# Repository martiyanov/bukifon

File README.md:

# Букифон (Bukifon) — открытая платформа: сэмплер + синтезатор + модули

**Версия: 0.57.0** · сайт: **https://bukifon.ru/** (канон, HTTPS), `bukifon.com` → 301, зеркало: https://martiyanov.github.io/bukifon/ (см. [`VERSION`](VERSION), [`CHANGELOG.md`](CHANGELOG.md))

**Букифон** — настольный музыкальный инструмент-платформа, который собирается из
доступных компонентов, печатается на 3D-принтере, расширяется модулями и полностью
открыт: схемы (KiCad), прошивка (C++), механика (STL/генератор), документация.

## Народный синтезатор

Букифон задуман как **народный инструмент**: доступный, повторяемый и открытый. Целевые
ориентиры комплекта (без печати и работы): «народный» на ESP32-S3 — **≤ $200**,
«стандарт» на ESP32-P4 — **≤ $300**, «полный» с аналоговыми картриджами — **≤ $400**.
Подробности и cost-down план — [spec/00-vision.md §13](spec/00-vision.md).

## Что это по сути

Один корпус **380 × 210 × 63 мм**, три режима:

- **Sampler** (в духе Elektron Digitakt) — сэмплы, запись/импорт по USB-C и SD,
  срезы, гранулярность, insert-FX, p-locks, условия триггеров;
- **Synth** (в духе Elektron Syntakt) — 4 части, 8 голосов, 4-оп FM, wavetable,
  ZDF-фильтры, лестница Муга, 3D-мод-матрица 16 слотов;
- **Hybrid** — сэмплы как источники синтеза, общий секвенсор и мод-матрица.

Плюс **режим компьютерной клавиатуры/контроллера**: USB-C композит (HID-клавиатура + MIDI +
UAC2 аудио), DAW-режим (16 энкодеров как CC, transport), **Wi-Fi и Bluetooth** (BLE-MIDI,
BLE HID, передача проектов). То есть Букифон — ещё и необычная механическая клавиатура
с 16 ручками.

**Свои модули может писать каждый:** программный модуль (SDK `BukifonModule`, C++/Lua),
аналоговый картридж на шине 26-pin или сменная панельная дека (18 пэдов / 42 клавиши).
Подробнее — [spec/00-vision.md §12](spec/00-vision.md).

## Текущее состояние (v0.57.0)

| Блок | Состояние |
|---|---|
| **Панель v0.4** | 380 × 210 × 3 мм: 42 клавиши Lapka-42 (точная геометрия, ±18°), 16 энкодеров Ø14, экран 5.0″ 800×480 без рамки, 10 mini-jack, 2 фейдера 60 мм; пересечений 0 |
| **Корпус v0.5-B** | **клин 8°**: 380 × 210 × 61.5 мм (перед 32 / зад 61.5), 6 деталей watertight, печать без поддержек 279 г / 18.3 ч, fitcheck 32/0, профиль 1:1 для картонной проверки |
| **EXT в прошивке** | 8 MIDI-треков (CH/PC/vel/len, 1 CC p-lock), clock out/in 24 ppqn, GEN на внешних, live record, save/load EXTP+CRC32, DIN+USB без дублей; UI-вкладка EXT; **407/407 тестов** (`docs/70 §7`) |
| **Микрофон/голос (реализовано)** | PANEL-2 rev.3: **ICS-43434 I2S MEMS** + порт Ø1.8 (122, 5.5) + LED; CORE-2 rev.3: I2S1 GPIO40/41/42 + J19 + 3.5 мм jack/MAX9814/TS5A + SW3 mute; прошивка: захват/запись ≤30 с/битбокс kick-snare-hat/UNDO/приватность/UI MIC; **407/407 тестов** |
| **Идея → звук** | метрики интуитивности в docs/68: time-to-sound ≤10 с, time-to-idea ≤30 с, 0 критических ошибок за 5 мин, blind-тест 5 людей |
| **Module SDK v0.2** | манифест `bukifon.module.v2` (schema/id/version/api/abi/permissions/params/sha256), валидатор + безопасный loader (API/ABI/SHA до исполнения), 2 примера (`mod_tape_delay`, `mod_euclid_arp`), упаковка `--check` |
| **Внешний секвенсор** | **8 MIDI-треков + 4 внутренние партии**: channel/PC/vel/length, clock out/in, p-lock CC, GEN на внешних, live record; паритет с Octatrack по MIDI (`docs/70`) |
| **Философия интерфейса** | «конституция»: 10 принципов, зеркальная карта ручка↔ячейка, грамматика жестов (`docs/68`) |
| **Читаемость** | экран 5″ 800×480 = 188 PPI, пиксель 0.135 мм; шкала 12/18/24–28 px, проверка по угловым минутам и контрасту (`docs/69`) |
| **Демо = панель** | раскладка как у реального синтезатора (16 энкодеров вокруг экрана, 10 джеков сверху, кластеры ±18°, фейдеры между кластерами); проверка `tools/check_demo_layout.js` → LAYOUT OK (`docs/67`) |
| **Внешнее ревью** | ChatGPT-ревью (`tools/chatgpt_review.sh`, Codex) — 10 рисков, 5 изменений; внедрены контекст-строка/HOME/UNDO/COMPARE/Shift-overlay (`docs/reviews/`, `docs/65 §4a`) |
| **UX-паттерны** | исследование синтезаторных практик (Elektron, Kaleidoscope Минкина, Nord/Deluge/OP-1/Push/M8) и рубрика 9/10 — `docs/65`; GEN-страница, мультивыбор, пресеты, A/B, mod-индикация в демо |
| **Home offload** | `tools/home_offload.sh` — rsync+SSH на домашний ПК (8 ядер, RTX 3060); host-тесты прошли там 226/226 |
| **Темы в прошивке** | 4 темы × 12 токенов (docs/62), рендер на токенах, CLI `--theme`, **226/226 тестов** |
| **UI/UX** | 3 итерации, 16 энкодеров (8 страниц + 8 макросов), фейдеры TRACK/SCENE/DJ + Fn, REC-ресемплинг, 4 темы экрана 800×480 (`docs/61–64`) |
| **Кириллица** | 66 глифов 6×8 (А–Я, а–я, Ё/ё), UTF-8 lookup, транслитерация удалена; метрика: max 90 px при ячейке 94 px; 10 скриншотов RU/EN |
| **Локализация** | UI RU/EN: 90+ ключей (`tr()`), переключение и сохранение языка (project v2), **кириллический glyph-пакет 6×8 (66 глифов, транслитерация удалена)**, 10 RU/EN-скриншотов |
| **Хранение** | storage backend (MockFlash/SD/NVS-stub), **атомарная A/B запись** с CRC32 и recovery; project v2, preset bank, язык — через backend; power-cut/bit-flip тесты |
| **Проект v2** | `.bkfp`: 4 партии + 8 EXT-треков + GEN + mic + модули + тема/транспорт, CRC32, миграция v1, транзакционная загрузка |
| **P4 bring-up app** | UART-баннер/чип/PSRAM, I2C-скан 8/8, RGB565-паттерны, engine bench ≤650 µs, I2S MEMS 1 с; **сборка 330 512 Б, 0 warnings** (IDF 5.5, home) |
| **P4 toolchain** | **сборка проверена** на `pole`: ESP-IDF v5.5 → `bukifon_p4.bin` 250 КБ (83 % app-раздела свободно), bootloader+table; PlatformIO P4 по-прежнему не умеет (`docs/59`) |
| **Демо RU/EN** | 256 ключей, переключатель RU/EN (URL `?lang=en`, localStorage), canvas через `t()`; **a11y**: роли/aria, клавиатурные энкодеры/фейдеры/джеки, видимый фокус, live-region; UX-тест 8/8 RU и EN |
| **Веб-демо** | интерактивная модель: [martiyanov.github.io/bukifon/demo](https://martiyanov.github.io/bukifon/demo/) — 42 клавиши, 16 энкодеров, секвенсор, FM-звук, 4 режима (`docs/58`) |
| **Закупки** | единый лист: P1 $426 + PWR $276.92 + LCD-адаптер $72.8 + печать $42 ≈ **$784** с зачётом пересечений (`docs/54`) |
| **Серийники/QR** | `tools/make_labels.py` (A4 3×8, 60×30 мм, QR+manifest), identity 114 B + двухслотовая flash-модель (`docs/55`); **216/216 тестов** |
| **Протокол P1** | 8 сценариев, пороги, пустые таблицы, матрица P4/H743 + CSV-форма (`docs/56`) |
| **LCD-адаптер** | FFC-40 breakout для HotLCD ST7262 (31×0R pinout-jumper, 35 TP, JST подсветки), ERC 0/0 — проверка экрана на стенде до PCB (`docs/49`) |
| **Release bundle** | `tools/make_release_bundle.sh` → 339 файлов / 15 МБ, SHA256SUMS; `RELEASE_BUNDLE.md`, `docs/50` |
| **Медиа** | PNG→JPEG (60 файлов, −83 МБ), SVG→.svg.gz (19, −46 МБ), дубликаты убраны; tracked **71 МБ** (`docs/52`) |
| **Дисплей** | RGB565 поверх RGB888 FPC-40: **TFT-H050A1SVIST4R40** (HotLCD/ST7262, 40-pin, 1000 нит, $18–25), резерв NHD/EJ050NA; DSI — rev.3.1 (`docs/47`) |
| **PWR-стенд** | 13 измерений до PCB (`docs/44`); BOM: база $123.92 + EVM $153 = **$276.92** (вариант A, D-79); breadboard запрещён |
| **Fab dry-run** | 4 пакета `fab/*/rev1-scaffold`: 16 Gerber-слоёв, PTH+NPTH (129/45/45/4 отверстий), CPL⊆BOM, Edge.Cuts, **checker PASS**; `tools/export_fab_dryrun.sh` — проверка пайплайна до заказа |
| **P4 NVS/partitions** | `partitions.csv` (nvs 24K, factory 1 MiB, storage 1 MiB, coredump 64K), real NVS backend, self-test `project.meta`/`lang`; **bin 369 552 Б, 65 % factory свободно** |
| **PCB rev.1: статус** | 0 placeholder, но **328 упрощённых падов** и GND без заливки: полные реальные пассивы/зоны **не проходят DRC** на 200×108 при 373 компонентах — оставлен DRC-clean каркас (0/0); скрипты упаковки/зон сохранены до трассировки после MCU freeze (docs/82 §12, D-105) |
| **PCB rev.1: реальные футпринты** | **0 placeholder**; кастомные `.kicad_mod` (P4-адаптер, C6, MP1584, Choc) + стандартные KiCad (TRS/DC/кнопки/QFN); DRC-классы Default/Power/USB_HS(90 Ω)/Audio/RF; **DRC 0/0**, RULES PASS; план GND-полигонов |
| **PCB rev.1: нетлист + футпринты** | CORE-2 **373 refs/1224 пада** (16 placeholder), PANEL-2 left/right 181/174 (по 21 Choc), PWR-2 128 (0 placeholder); **DRC 0/0**, verify PASS; unconnected — неразведённые цепи |
| **PCB rev.1 scaffolds** | KiCad-каркасы: CORE-2 200×108 6L, PANEL-2 2×180×190 4L, PWR-2 90×70 4L/2oz; Edge.Cuts/NPTH/keepout, **DRC 0/0**, verify ±0.05 мм (`hardware/*/rev1/`) |
| **Раскладка Lapka-42** | клавиши PANEL-2 исправлены: каждая плата — свои 21 (L01–L21 / R01–R21) по spec (остаточное 0.006 мм от Lapka-42), DRC 0/0; превью `docs/assets/panel-lapka-*.png` |
| **Вырезы разъёмов** | **11 задних**: MIDI IN/OUT **TRS-A Ø8.2** (X30/44), DC Ø9 X91, EXP Ø8.2 X120.5, mic Ø8.2 X140, **LINE OUT** (стерео TRS) X160, PHONES X172, AUDIO IN L/R X184/196, **CV5/6** X208/220; SD 12×2, USB-C; перемычки ≥3.8 мм; B-light **228.9 г/11.0 ч**; fitcheck 16/0 |
| **Board-fit (PCB rev.1)** | контуры для KiCad: CORE-2 200×108, PANEL-2 две платы 180×180 (360×190), PWR-2 90×70; DXF/assembly/spec, 22 проверки 0 конфликтов (`mechanical/board-fit/`) |
| **PANEL-2 ∥ панели** | стойки/плата наклонены вместе с панелью: угол **0.00°**, зазор **12 мм**, оси энкодеров/клавиш ⊥ панели; fitcheck B-light **47/0**; B-light **228.9 г/11.0 ч**; `panel_parallel.jpg` |
| **Корпуса** (с микрофоном) | B_mic ≈278 г/18.4 ч, C_mic ≈316 г/20.9 ч (порт/LED/MEMS на панелях; fitcheck 44/0 и 49/0) |
| **Корпуса** | A flat 301 г/19.9 ч · B 8° 275.5 г/18.2 ч · **B-light 228.9 г / 11.0 ч** · C 12° 313.2 г/20.7 ч; B_mic 276.8, C_mic 314.6; PANEL-2 ∥ панели (0.00°) — `docs/45` |
| **Factory test** | 14 тестов, CLI `factory --json`, loopback-плаг, EOL 2–2.5 мин (`docs/46`); **183/183 тестов** |
| **Product BOM P4 (первый SKU)** | `BOM-p4.csv` + `docs/33/40` (rev.3 с микрофоном): COGS **$241/$215/$196** на 1/10/25 (mic-узел $17.6); **P4 Standard $299** (gross 28.1 % на 10, net ~18 %), Full Bundle $399; S3 lite — $224/$199/$181 |
| **Сборка** | `renders/templates/bukifon_assembly_map_1to1.pdf` (4 стр: слои, панель 1:1, крепёж/шлейфы), `docs/34`, `docs/35` print-first, 3D exploded |
| **UI = философия** | 16 ячеек зеркально ручкам, шкала 12/18/24–28 px, контекст-строка, HOME; Cream AA; **263/263 тестов** (`docs/66/68/69`) |
| **GEN/UX в прошивке** | PROB/EUCLID/MUTATE/SCALE/ARP/EVOLVE/SEED (детерминированно), 5-я вкладка GEN, 8 пресетов с CRC32, A/B, мультивыбор, mod-visible «M»; **248/248 тестов** (`docs/66`) |
| **Прошивка v0.7** | **160/160 тестов**; S3 HAL сборка SUCCESS; spike `spike_s3` SUCCESS; **P1 P4-профиль** PASS (RGB/DSI 52 fps, HS UAC2 8×8, max block 320 µs); UI 4 режимов; Module API v0.1 |
| **CORE-2 rev.2 (основная плата)** | ESP32-P4 + ESP32-C6, 32 МБ PSRAM, USB HS, RGB565/DSI, ERC 0/0; DFM/DFT: 30 TP, **21 self-test** (вкл. микрофон), recovery, 6 слоёв — PRE-FREEZE |
| **Корпус B-light** | **228.9 г / 11.0 ч** (−17 % массы, −39 % времени): стенки 2.0/дно 1.8, 3 периметра + локальные рёбра, панели-оболочки; 6 STL watertight, fitcheck **47/0**; PANEL-2 ∥ панели |
| **CORE-2 rev.2** | схема внесена: J17/J18, входы 12V_EXT/N12_EXT/+5V_EXT/5V_LED, EN-развязки, CV IN3/4 на MCP3208, re-pin J14/J15/J16, DNP 46; **ERC 0/0**, pinmap PASS |
| **PANEL-2 rev.2** | J13/J14 (5V_LED, LED_RET, EN_RAILS, EN_LED5), re-pin по канону, GATE_IN на MCP23017 0x23, LED_DATA 3.3 В + shifter; **ERC 0 err/6 warn**, verify 1290/0 |
| **PWR-2 rev.1** | батарея 1S2P + BMS BQ297 + **MAX17048** + рельсы шины: +12 В 330 мА (TPS61088), −12 В 95 мА (LMR33630 IBB), +5 В 1.6 А, +5V_LED; master load-switch, EN рельсов, питание только от BQ24074 OUT/VSYS; ERC **0/0**, PRE-FREEZE |
| **Электроника rev.1** | **CORE-2** (ESP32-P4 + ESP32-C6 Wi-Fi/BLE по SPI, USB HS composite, аудио PCM5102A/PCM1808, CV, MIDI, шина) — ERC **0/0**, pinmap PASS (54/55 GPIO), **PRE-FREEZE**; **PANEL-2** (16 энкодеров + 42 клавиши через 4× MCP23017, LCD, 10 джеков, 2 фейдера, 3 шлейфа) — ERC 0 errors / 6 warnings, **PRE-FREEZE**. Не заказывать до бенчмарка P1 |
| **Прошивка v0.6** | host-демо UI 800×480, секвенсор 4×16 (хранение 8 дорожек), save/load с CRC16, Module API v0, режимы Synth/Sampler/DAW/USB-keyboard, каркасы USB composite и BLE/Wi-Fi; **120/120 тестов**; сборки ESP32-S3 и RP2040; P4 — toolchain пока нет |
| **P1-стенд** | `docs/26` — что купить (P4 EV, H743, S3, PCM5102A/1808, дисплей, SD, БП/нагрузка), схема стенда, протокол измерений и таблица решения; без стенда MCU не фиксируется |
| **Cost-down / первый SKU** | `docs/27`: product BOM вместо «мастерской», S3-base **kit $199** (партия 10–25, direct-sale), P4 $299 после P1, full $399 bundle; батарея — не россыпь 18650 |
| **Бумажный макет** | `renders/templates/bukifon_paperkit_1to1.pdf` (4 стр: панель 1:1 ×2, профиль 8°, карта 7 проверок) + `docs/28` |
| **Бенчмарк P1** | workload freeze + харнесс `firmware/bench` (7 сценариев, JSON/CSV, детерминизм, 0 аллокаций): host worst **218 µs** = 16.4 % дедлайна, 431 µs запаса до критерия 650 µs; `bench_s3` собран; **протокол приёма стендов P4/H743 готов** (`docs/56`, CSV-форма), стенды — следующие |
| **SDK модулей** | Module API v0 (10 функций, лимиты, WCET/bypass), каталог `modules/` (template + gain_fx C++ + LFO Lua), `tools/validate_module.py`, `tools/new_module.sh`, CI `modules.yml` |
| **BOM (draft)** | 92 позиции: база ≈ 21 657 ₽ (~$271), полный ≈ 32 518 ₽ (~$406); «народная» цель ≤ $200 / стандарт ≤ $300 — cost-down план в spec/00 §13 |
| **Безопасность** | история очищена от GPS EXIF и vendor-PDF с IP, санитизация путей, `SECURITY.md`, `tools/security_scan.sh` |

## Ключевые документы

| Документ | О чём |
|---|---|
| [spec/90-requirements-registry.md](spec/90-requirements-registry.md) | реестр требований R-01…, журнал решений D-01… — единственный источник истины |
| [docs/12-roadmap.md](docs/12-roadmap.md) | дорожная карта P0–P8 с числовыми критериями выхода |
| [docs/10-elektron-hardware.md](docs/10-elektron-hardware.md) | что стоит внутри Elektron (ColdFire, DSP56300, SHARC, FPGA) |
| [docs/11-esp32-feasibility.md](docs/11-esp32-feasibility.md) | можно ли на ESP32: расчёт нагрузки, P4/S3/H743/Teensy |
| [docs/03-second-opinion-mcu.md](docs/03-second-opinion-mcu.md) | независимое ревью плана (DeepSeek) |
| [docs/04-consultation-gpt.md](docs/04-consultation-gpt.md) | консультация GPT/Codex (gpt-5.6) по MCU и архитектуре |
| [docs/00-context-transfer.md](docs/00-context-transfer.md) | контекст проекта для передачи другим агентам |
| [PULL_REQUEST.md](PULL_REQUEST.md) | описание MR v0.4 |
| [docs/20-analog-projects.md](docs/20-analog-projects.md) | разведка аналогов (Deluge, M8, Polyend, Daisy, PreenFM, Norns…) |
| [docs/21-ergonomics.md](docs/21-ergonomics.md) | эргономика: клин 8°, 32/61.5 мм, экран 35° |
| [docs/22-night-plan.md](docs/22-night-plan.md) | ночной план и scope freeze |
| [docs/23-nightly-report.md](docs/23-nightly-report.md) | отчёт ночи: что готово/симулируется/нельзя заказывать |
| [docs/24-module-sdk.md](docs/24-module-sdk.md) | SDK модулей: Module API v0, упаковка, ограничения |
| [docs/25-power-architecture.md](docs/25-power-architecture.md) | питание: ±12 В, BQ24074, MAX17048, земля, стенд до PCB |
| [docs/26-p1-bench-kit.md](docs/26-p1-bench-kit.md) | P1-стенд: закупка, схема, протокол измерений, таблица решения MCU |
| [docs/27-costdown.md](docs/27-costdown.md) | cost-down, product BOM, первый SKU S3-kit $199, батарея, дефицит |
| [docs/28-paper-kit.md](docs/28-paper-kit.md) | бумажный макет 1:1 за 30 минут: 7 проверок эргономики |
| [docs/29-p1-order.md](docs/29-p1-order.md) | точный список заказа P1-стенда (что, где, сколько) |
| [docs/54-shopping-list.md](docs/54-shopping-list.md) | **единый закупочный лист**: P1 + PWR + LCD-адаптер + печать, итоги A–D, порядок |
| [docs/30-security-purge.md](docs/30-security-purge.md) | запрос на purge старых PII-объектов GitHub (SHA) |
| [docs/31-core-s3-constraints.md](docs/31-core-s3-constraints.md) | CORE-S3: GPIO 31, 1-bit SD, USB endpoint ceiling, RGB+1FB, TPS63802 |
| [docs/32-progress-report.md](docs/32-progress-report.md) | сводный отчёт v0.4→v0.13.0: вехи, блокеры, следующий шаг |
| [docs/49-lcd-adapter.md](docs/49-lcd-adapter.md) | LCD FFC-40 адаптер и pinout J12 |
| [docs/50-downloads.md](docs/50-downloads.md) | где скачать STL/PDF/BOM/прошивку |
| [docs/51-pwr-log.md](docs/51-pwr-log.md) | журнал 13 измерений PWR и матрица go/no-go |
| [docs/52-media-policy.md](docs/52-media-policy.md) | форматы медиа и размер репозитория |
| [docs/54-shopping-list.md](docs/54-shopping-list.md) | единый закупочный лист до PCB |
| [docs/55-labels-traceability.md](docs/55-labels-traceability.md) | серийники, QR-метки, traceability |
| [docs/56-p1-measurements.md](docs/56-p1-measurements.md) | протокол P1: P4 vs H743 |
| [docs/57-usability-test.md](docs/57-usability-test.md) | тест эргономики на макете |
| [docs/58-web-demo.md](docs/58-web-demo.md) | веб-демо интерфейса и звука |
| [docs/59-p4-toolchain.md](docs/59-p4-toolchain.md) | P4: ESP-IDF scaffold и сборка |
| [docs/60-module-distribution.md](docs/60-module-distribution.md) | упаковка и распространение модулей |
| [docs/61-ui-design.md](docs/61-ui-design.md) | UI/UX: итерации и лучшие практики |
| [docs/62-screen-palette.md](docs/62-screen-palette.md) | палитра экрана 800×480 (4 темы) |
| [docs/63-resampling-looper.md](docs/63-resampling-looper.md) | ресемплинг (v1.0) и луппер (backlog) |
| [docs/64-fader-modes.md](docs/64-fader-modes.md) | режимы фейдеров: Octatrack-сцены, DJ, Fn |
| [docs/65-ux-patterns.md](docs/65-ux-patterns.md) | UX-паттерны синтезаторов, связка с железом, рубрика 9/10 |
| [docs/66-ux-implementation.md](docs/66-ux-implementation.md) | реализация UX-паттернов: GEN, пресеты, A/B, мультивыбор |
| [docs/67-panel-demo-layout.md](docs/67-panel-demo-layout.md) | сверка раскладки демо с панелью v0.4 |
| [docs/68-interface-philosophy.md](docs/68-interface-philosophy.md) | философия интерфейса и продукта (конституция) |
| [docs/69-screen-legibility.md](docs/69-screen-legibility.md) | читаемость экрана 800×480: физика, шрифты, контраст |
| [docs/70-external-sequencer.md](docs/70-external-sequencer.md) | Букифон как секвенсор для внешних синтезаторов |
| [docs/71-mic-voice.md](docs/71-mic-voice.md) | микрофон/голос: запись, битбокс, вокодер, приватность |
| [docs/72-assembly-workshops.md](docs/72-assembly-workshops.md) | где собрать: мастерские Москвы/СПб/НН, RFQ, цены |
| [docs/73-morning-report.md](docs/73-morning-report.md) | утренний отчёт: состояние, блокеры, план, риски |
| [docs/74-usability-test-harness.md](docs/74-usability-test-harness.md) | blind UX-тест: 8 задач, таймер, JSON (`/demo/?test=1`) |
| [docs/75-release-readiness.md](docs/75-release-readiness.md) | ворота G1–G12 до v1.0-rc, статусы, stop/go |
| [docs/76-known-limitations.md](docs/76-known-limitations.md) | честные ограничения v1.0-rc (до покупки) |
| [docs/77-quick-start.md](docs/77-quick-start.md) | быстрый старт: идея за 10 минут |
| [docs/78-support-repair.md](docs/78-support-repair.md) | поддержка/ремонт: диагностика, recovery, запчасти, гарантия |
| [docs/79-competitors-2026.md](docs/79-competitors-2026.md) | аналоги 2025–2026, позиционирование и цены |
| [docs/80-day1-bringup.md](docs/80-day1-bringup.md) | день 1 с железом: PWR→P1→CORE-2, 15 шагов, stop/go |
| [docs/81-faq.md](docs/81-faq.md) · [docs/press/](docs/press/) | FAQ для покупателя · пресс-кит (буилерплейт RU/EN, изображения) |
| [docs/82-pcb-layout-plan.md](docs/82-pcb-layout-plan.md) | план разводки rev.1: стеки, floorplan, DRC/DFM, критичные цепи |
| [docs/83-fab-package.md](docs/83-fab-package.md) · [fab/](fab/) | состав fab-пакета, CPL/BOM, чек-лист, приёмка; `tools/check_fab_package.py` |
| [docs/84-costdown.md](docs/84-costdown.md) | cost-down: где деньги, варианты снижения, маржа $299/$319/$349 |
| [docs/85-second-source.md](docs/85-second-source.md) | вторые источники, supply-риски, чек-лист до заказа |
| [docs/86-backlog-webapp-plugin.md](docs/86-backlog-webapp-plugin.md) | бэклог: сайт на VDS, PWA-приложение, DAW-плагин |
| [docs/91-software-modules.md](docs/91-software-modules.md) | софтовые модули/машины: `.bkm`, USB/SD/Wi-Fi, sandbox, каталог |
| [docs/87-v1.0-rc-notes-draft.md](docs/87-v1.0-rc-notes-draft.md) | черновик release notes v1.0-rc (критерии, проверки) |
| [docs/88-vds-deploy.md](docs/88-vds-deploy.md) | деплой сайта на VDS (bukifon.ru/.com): DNS, TLS, скрипт |
| [docs/en/README.md](docs/en/README.md) · [quick-start](docs/en/quick-start.md) | English docs index / quick start |
| [docs/72-assembly-workshops.md](docs/72-assembly-workshops.md) | где собрать: мастерские Москвы/СПб/НН, RFQ, цены |
| [docs/73-morning-report.md](docs/73-morning-report.md) | утренний отчёт: состояние, блокеры, план, риски |
| [docs/74-usability-test-harness.md](docs/74-usability-test-harness.md) | blind UX-тест: 8 задач, таймер, JSON (`/demo/?test=1`) |
| [docs/75-release-readiness.md](docs/75-release-readiness.md) | ворота G1–G12 до v1.0-rc, статусы, stop/go |
| [docs/76-known-limitations.md](docs/76-known-limitations.md) | честные ограничения v1.0-rc (до покупки) |
| [docs/77-quick-start.md](docs/77-quick-start.md) | быстрый старт: идея за 10 минут |
| [docs/78-support-repair.md](docs/78-support-repair.md) | поддержка/ремонт: диагностика, recovery, запчасти, гарантия |
| [docs/79-competitors-2026.md](docs/79-competitors-2026.md) | аналоги 2025–2026, позиционирование и цены |
| [docs/80-day1-bringup.md](docs/80-day1-bringup.md) | день 1 с железом: PWR→P1→CORE-2, 15 шагов, stop/go |
| [docs/81-faq.md](docs/81-faq.md) · [docs/press/](docs/press/) | FAQ для покупателя · пресс-кит (буилерплейт RU/EN, изображения) |
| [docs/82-pcb-layout-plan.md](docs/82-pcb-layout-plan.md) | план разводки rev.1: стеки, floorplan, DRC/DFM, критичные цепи |
| [docs/83-fab-package.md](docs/83-fab-package.md) · [fab/](fab/) | состав fab-пакета, CPL/BOM, чек-лист, приёмка; `tools/check_fab_package.py` |
| [docs/84-costdown.md](docs/84-costdown.md) | cost-down: где деньги, варианты снижения, маржа $299/$319/$349 |
| [docs/85-second-source.md](docs/85-second-source.md) | вторые источники, supply-риски, чек-лист до заказа |
| [docs/86-backlog-webapp-plugin.md](docs/86-backlog-webapp-plugin.md) | бэклог: сайт на VDS, PWA-приложение, DAW-плагин |
| [docs/91-software-modules.md](docs/91-software-modules.md) | софтовые модули/машины: `.bkm`, USB/SD/Wi-Fi, sandbox, каталог |
| [docs/87-v1.0-rc-notes-draft.md](docs/87-v1.0-rc-notes-draft.md) | черновик release notes v1.0-rc (критерии, проверки) |
| [docs/88-vds-deploy.md](docs/88-vds-deploy.md) | деплой сайта на VDS (bukifon.ru/.com): DNS, TLS, скрипт |
| [docs/en/README.md](docs/en/README.md) · [quick-start](docs/en/quick-start.md) | English docs index / quick start |
| [docs/53-pwr-log.md](docs/51-pwr-log.md) | журнал 13 измерений PWR и go/no-go |
| [docs/33-bom-s3.md](docs/33-bom-s3.md) | product BOM S3-base: COGS 1/10/25, опции, маржа |
| [docs/34-assembly.md](docs/34-assembly.md) | пошаговая сборка S3-base (B-light) |
| [docs/35-print-first.md](docs/35-print-first.md) | что печатать первым и как проверить жёсткость |
| [docs/36-rc-definition.md](docs/36-rc-definition.md) | Definition of Done для v1.0-rc (S3-base) |
| [docs/37-compliance.md](docs/37-compliance.md) | RED/GPSR, батарея, EMC, SBOM, гарантия, SKU-экономика |
| [docs/05-benchmark-workload.md](docs/05-benchmark-workload.md) | workload freeze P1 и критерии |
| [docs/05a-benchmark-howto.md](docs/05a-benchmark-howto.md) | как запустить бенчмарк на S3/P4/H743 |
| [docs/56-p1-measurements.md](docs/56-p1-measurements.md) | **протокол P1 P4 vs H743**: стенд, 8 сценариев, пороги, матрица решения, fallback H743 |
| [docs/p1-results-template.csv](docs/p1-results-template.csv) | машиночитаемая форма результатов P1 (P4/H743 × 8 сценариев) |
| [modules/](modules/) | каталог модулей: шаблон, примеры gain_fx и LFO |
| [firmware/bench/](firmware/bench/) | харнесс P1 (fm/granular/mix/psram/ui/usb, JSON/CSV) |
| [SECURITY.md](SECURITY.md) | политика безопасности и приватности |

## Компоновка панели v0.4

Канон — [`spec/panel-spec-v0.4.json`](spec/panel-spec-v0.4.json) (координаты всех элементов в мм).
Печать 1:1: [renders/templates/bukifon_v04_panel_1to1.pdf](renders/templates/bukifon_v04_panel_1to1.pdf)
(**A3** 420×297) или [4×A4 с перекрытием](renders/templates/bukifon_v04_panel_tiles_A4.pdf); печатать 100 %, проверить линейку 50 мм.

| Элемент | Координаты (мм) |
|---|---|
| Клавиши | 2 × 21 Lapka-42, Choc 18 × 17, половины ±18°, кластеры центром (83, 148) и (297, 148) |
| Энкодеры Ø14 | X = 25.2 / 54.1 / 82.6 / 111.4 и 269.3 / 297.8 / 326.6 / 355.8; Y = 35.7 / 68.5 |
| Экран 5.0″ | вырез 108 × 64.8, центр (190, 58.7), без рамки |
| Mini-jack 3.5 | 10 шт., X = 129.9…247.8 (шаг 13.1), Y = 10.5 |
| Фейдеры | X = 175.1 / 204.0, центр Y = 150, прорезь 2.5 × 63 |
| Динамики | **нет** (по ТЗ) |
| Разъёмы под экраном | **нет** (по ТЗ) |

Превью: [renders/templates/bukifon_v04_render.png](renders/templates/bukifon_v04_render.png),
сравнение с концептом заказчика: [renders/templates/bukifon_v04_vs_concept.jpg](renders/templates/bukifon_v04_vs_concept.jpg).

## 3D-печать (корпус v0.4)

- STL/3MF: [`mechanical/stl_v04/`](mechanical/stl_v04/) — panel_L/panel_R, body_L/body_R, foot, keycap;
  сборка `bukifon_v04_assembly.3mf`;
- рендеры: [`mechanical/preview_v05_compare/`](mechanical/preview_v05_compare/) (сравнение вариантов, изометрия, вид сверху,
  наложение на 2D-эталон, разнесённый вид, close-up);
- параметры печати и время: [mechanical/prints.md](mechanical/prints.md);
- сборка: [mechanical/assembly.md](mechanical/assembly.md), проверки: [mechanical/fit_check.md](mechanical/fit_check.md).

## Сборка прошивки (прототип RP2040)

```bash
export PLATFORMIO_CORE_DIR=/tmp/piocore
/tmp/msvenv/bin/pio run -d firmware/Bukifon      # сборка UF2
cd firmware/host && make test                    # host-тесты DSP (407 тестов)
```

## Структура репозитория

Текущее — в рабочих папках; старые версии доступны в **git-тегах** и `dist/bukifon-fresh-*.bundle` (архивные папки удалены 06.11.2025 для чистоты дерева); карта — [STRUCTURE.md](STRUCTURE.md).

```
spec/            требования, архитектура, электрика, механика, прошивка, реестр требований
docs/            обзор, гайд сборки, лицензии, ревью MCU, консультация GPT, дорожная карта
hardware/        KiCad: CORE-1, PANEL-1, деки, аналоговые модули, питание
firmware/        прошивка (движок, драйверы, UI, тесты)
mechanical/      параметрический генератор корпуса, STL/3MF, рендеры, печать/сборка
tools/           генераторы раскладок, печатных листов, трассировка концепта
renders/         шаблоны 1:1 и превью (templates/)
refs/            эскизы и фото заказчика, пакет handoff v0.3
BOM.csv          сводный BOM
```

## Версионирование

SemVer + аннотированный тег на каждый релиз. Правила — в [AGENTS.md](AGENTS.md).
История — [CHANGELOG.md](CHANGELOG.md). Теги: `v0.1.0` (прототип 315×145), `v0.2.0`
(печатные листы), `v0.3.0` (раскладка 380×210), `v0.4.0` (канон v0.4).

## Лицензии и атрибуция

- аппаратура и механика — CERN-OHL-S-2.0;
- прошивка — GPL-3.0-or-later;
- документация — CC BY-SA 4.0;
- раскладка Lapka-42 — атрибуция braindefender/lapka-42 (см. [NOTICE](NOTICE)).

## Репозиторий

**https://github.com/martiyanov/bukifon** — `main` (стабильная ветка), работа ведётся
в `feature/panel-v04-canonical` до слияния MR.

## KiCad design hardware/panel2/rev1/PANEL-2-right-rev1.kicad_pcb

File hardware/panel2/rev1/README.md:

# PANEL-2 rev.1

## Раскладка клавиш (исправлено 06.11.2025)

Клавиши размещены **по spec/panel-spec-v0.4.json** (точная геометрия Lapka-42,
upstream `braindefender/lapka-42`): левая плата — `KEY_L01…L21`, правая — `KEY_R01…R21`,
координаты/углы из `controls.keyboard_left/right`. Ранее refs делились по номеру без L/R —
клавиши накладывались; исправлено, DRC 0/0. Превью — `docs/assets/panel-lapka-*.png`. — PCB scaffolds left/right (PRE-FREEZE)

> **Не заказывать PCB.** Каркасы двух плат 180×190 из `mechanical/board-fit/`: контур с
> вырезами джеков, крепёж, keepout-зоны, стек 4 слоя. Нет посадочных мест/связей/меди.

## Файлы

| Файл | Что |
|---|---|
| `PANEL-2-left-rev1.kicad_pcb` | левая плата 180×190, 3×M3 (H1–H3), 5 вырезов J01–J05, keepout экрана/энкодеров/клавиш/фейдера/MIC_LED |
| `PANEL-2-right-rev1.kicad_pcb` | правая плата 180×190, 3×M3, 5 вырезов J06–J10, keepout + батарея |
| `*.svg/.pdf` | контур + шелкография |
| `*.drc.rpt` | DRC: **0 нарушений, 0 unconnected** на каждой |
| `../core2/rev1/gen_scaffold.py` | общий генератор (запускать из корня: `python hardware/core2/rev1/gen_scaffold.py`) |
| `../core2/rev1/verify_scaffold.py` | сверка с board-spec ±0.05 мм — **PASS** |

## Параметры

- Контуры: 180×190 мм каждая (левая origin 10;10, правая 190;10), площадь 34 200 мм².
- Крепёж: 3×M3 Ø3.4 (NPTH) на каждой.
- Вырезы джеков: Ø8.2 по задней кромке (J01–J05 / J06–J10), дуги точно по радиусу 4.1 мм из board-spec.
- Стек: 4 меди (F.Cu / In1 / In2 / B.Cu), 1.6 мм, 1 oz.
- Keepout: экран (без меди/высоких), 8 энкодеров Ø16, 21 клавиша, фейдер, MIC_LED,
  батарея (правая), джеки Ø10.
- PANEL-2 — **две платы** по шву X=190 (механический разрез панели 193+190 — 3 мм шип панели, не платы).

## Проверки

- DRC: 0 errors/warnings/unconnected на обеих.
- Сверка ±0.05: контуры, по 3 отверстия, 5 вырезов (радиус 4.1), 37 keepout-зон, 4 Cu, 1.6 мм — PASS.

## Что дальше

1. Импорт netlist/посадочных мест PANEL-2 rev.2 (экраны/клавиши/энкодеры/джеки/MCP23017).
2. FPC-40/IDC pinout и направление выхода (docs/82 §...); зоны MEMS ≥10 мм от LED/BL.
3. Крепёж: по board-fit **3×M3 на каждую плату (6 всего на панель)**; панель крепится к корпусу.
4. DFM `hardware/panel2/dfm.md`, затем заказ.

## Нетлист и посадочные места — первый импорт (2026-11-06)

- Источник: `hardware/panel2/PANEL-2.net` (PANEL-2 rev.2/3) + `BOM-panel2.csv`.
- Разбивка left/right по зонам board-fit: ENC1–8/KEY1–21/J01–J05/F1 — левая;
  ENC9–16/KEY22–42/J06–J10/F2 — правая; остальные refs — поровну.
- **Refs: left 181, right 174 (итого 355 + 6 H-креплений = 361)**.
- **Footprints: left 181 + 4 крепления, right 174 + 3 крепления**; pads left 585 / right 443.
- **Placeholder: 21 на каждой плате** — клавиши Choc (`KEY_L01…L21`, `KEY_R01…R21`);
  остальные (R/C/D/энкодеры/джеки) получили footprints из BOM (энкодеры/джеки — bare-имена
  кастомных библиотек, проверить при разводке).
- Зоны: энкодеры/клавиши/фельдеры/джеки — по центрам keepout/вырезов board-fit; остальное — сетка.
- **DRC: 0 errors / 0 warnings; unconnected: left 368 / right 265** — допустимо.
- Перегенерация: `python hardware/core2/rev1/gen_scaffold.py && python hardware/core2/rev1/import_netlist.py`.
- Дальше: реальные футпринты Choc/EC11/джеков/FPC-40/IDC, затем трассировка после MCU freeze.

## Реальные футпринты и DRC-правила (2026-11-06)

- **Placeholder'ы: 0** — 42 клавиши Choc заменены на custom `CHOC_V1` (18×18, 2 пада + NPTH
  центра 3.4/боковой 1.7, hot-swap) из `footprints/` (+`fp-lib-table`), вставлены pcbnew API.
- Остальные refs — footprint-имена из BOM (KiCad); в каркасе упрощённые пады (полные
  `.kicad_mod` — при разводке). Footprints left 181/right 174 (+крепёж), pads 630/488,
  refs 181/181 и 174/174; **DRC 0/0**, unconnected 367/264.
- **DRC-правила** (`.kicad_pro` left/right): классы Default/Power/USB_HS/Audio/RF, дорожки
  0.2–1.0 мм, via 0.6/0.3 и 0.8/0.45, diff pair 0.2/0.2; для каркаса silk/courtyard —
  `rule_severities` ignore.
- **GND-полигоны (план):** GND-заливка на F.Cu/B.Cu; аналоговое поле J14 — AGND-полигон,
  звезда; LED-цепочка — отдельный возврат к J13; экран/клавиши — без меди под FPC.

## Двусторонняя попытка (2026-11-06)

`rev1/two-sided/` — копии с реальными футпринтами на top+bottom и GND-зонами
(`build_two_sided.py`). DRC **FAIL** (упаковка courtyard/зазоры, zones_intersect) — в основную
версию **не промоутнуто**; main остаётся DRC 0/0 (328 упрощённых падов). Нужен floorplanner
после MCU freeze. Детали — docs/82 §13.

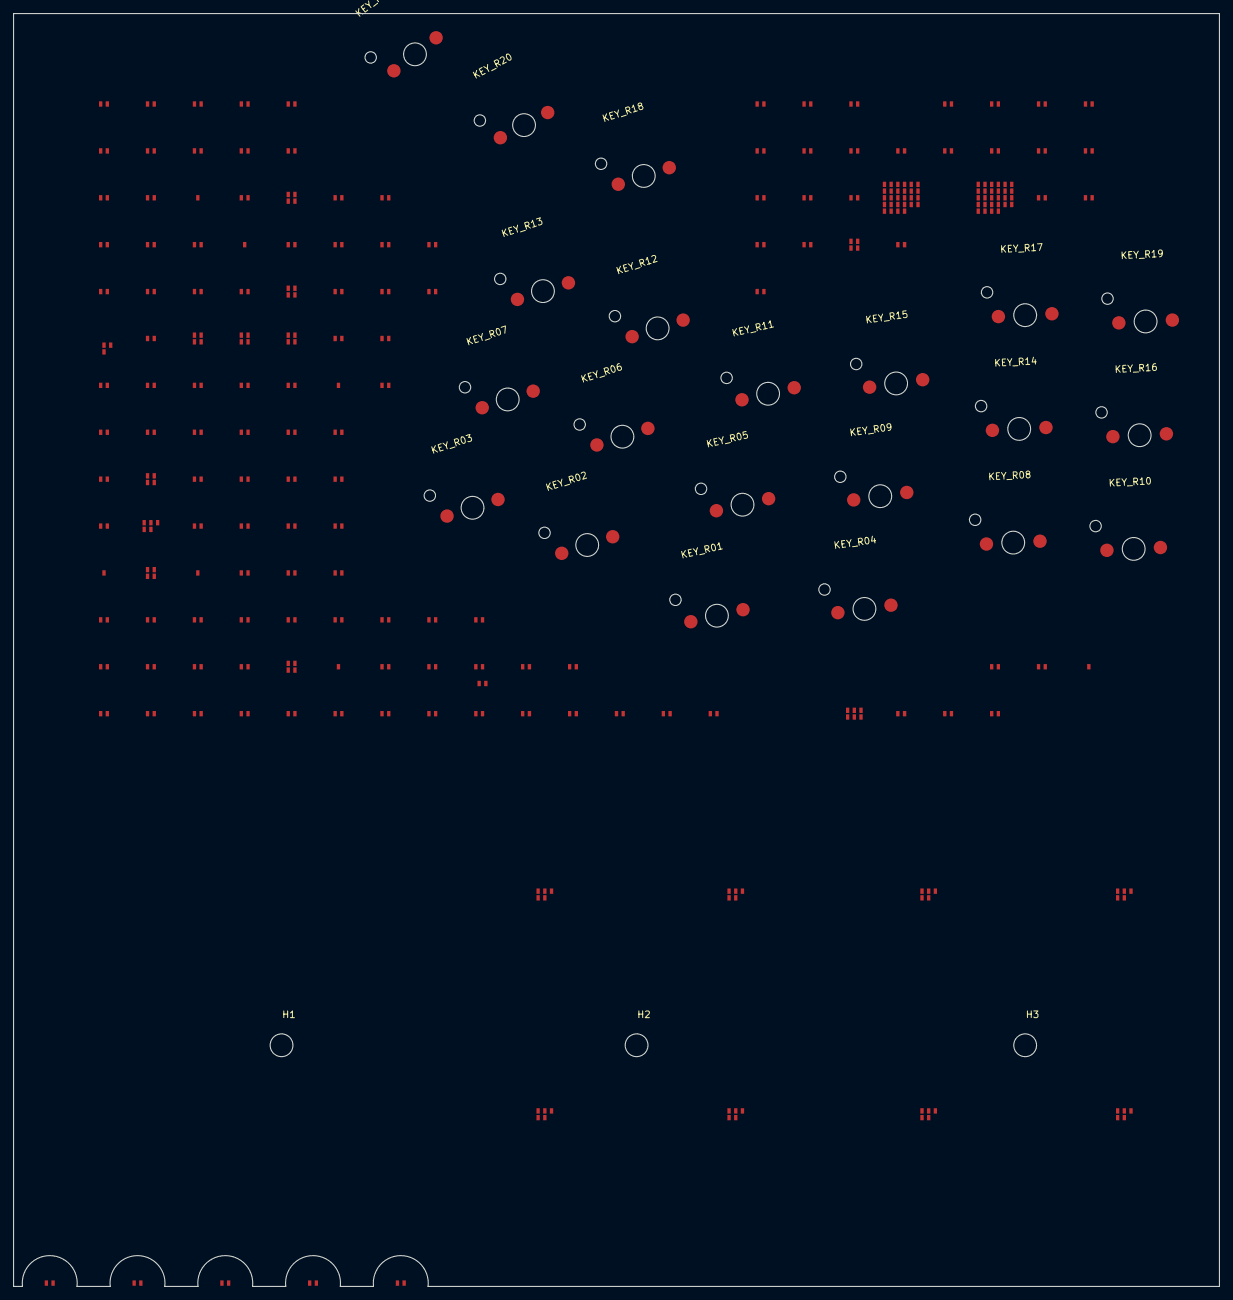
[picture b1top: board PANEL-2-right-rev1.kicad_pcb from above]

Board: 4 copper layers, 180.0 x 190.0 mm, 177 parts (0 on the bottom side), 95 nets, no tracks yet.

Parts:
C2, C4, C5, C6, C10, C12, C14, C16, C18, C21, C23, C25, C27, C29, C30, C32, C34, C36, C38, C42, C44, C46, C48, C51, C54, C56, C58, C61, C63, C65, C67, C69, C70, C72, C80, C82: 100n; C_0603_1608Metric
D1, D3, D6, D8, D11, D13, D15, D17, D19, D20, D22, D24, D26, D28, D31, D33, D35, D37, D39, D40, D42: 1N4148; D_SOD-323
D45, D47: SMAJ12A; D_SMA
D49, D50: SMAJ15A; D_SMA
D52: SMAJ5.0A; D_SMA
ENC9, ENC10, ENC11, ENC12, ENC13, ENC14, ENC15, ENC16: EC11; RotaryEncoder_Alps_EC11E-Switch_Vertical_H20mm
F2: POT60; Potentiometer_Bourns_PTA6043_Single_Slide
FB1: FB; L_Bourns_SRN6045TA
H1, H2, H3: MountingHole; MountingHole_M3_3.4mm
J06, J07, J08, J09, J10: JACK; Jack_3.5mm_CUI_SJ1-3523N_Horizontal
KEY_R01, KEY_R02, KEY_R03, KEY_R04, KEY_R05, KEY_R06, KEY_R07, KEY_R08, KEY_R09, KEY_R10, KEY_R11, KEY_R12, KEY_R13, KEY_R14, KEY_R15, KEY_R16, KEY_R17, KEY_R18, KEY_R19, KEY_R20, KEY_R21: Kailh Choc v1 hot-swap; CHOC_V1
LED_ENC3, LED_ENC5, LED_ENC7, LED_ENC9, LED_ENC10, LED_ENC12, LED_ENC14, LED_ENC16: WS2812B-2020; LED_WS2812B-2020_PLCC4_2.0x2.0mm
LED_STATUS: WS2812B-2020; LED_WS2812B-2020_PLCC4_2.0x2.0mm
R2, R4, R6, R8, R9, R10, R14, R16, R18, R21, R23, R25, R27, R29, R30, R32, R34, R36, R38, R41, R43, R45, R47, R81, R83, R85, R87: 10k; R_0603_1608Metric
R49, R50, R52, R54, R56, R58, R61, R63, R65, R67, R69, R70, R72, R74, R76, R78, R94, R96, R105, R114: 1k; R_0603_1608Metric
R98, R101: 100R; R_0603_1608Metric
R103, R110: 4.7k; R_0603_1608Metric
R112: 0R; R_0603_1608Metric
R120: 100k; R_0603_1608Metric
R122, R124: 33R; R_0603_1608Metric
SW1: SW_SPST; SW_DIP_SPSTx01_Slide_6.7x4.1mm_W7.62mm_P2.54mm_LowProfile
TP2, TP4, TP6, TP8, TP10, TP36, TP38: TP; TestPoint_Pad_D1.0mm
U1, U3: MCP23017; SOIC-28W_7.5x17.9mm_P1.27mm
U5: 74LVC1G17; SOT-23-5
U8: ICS-43434; InvenSense_ICS-43434-6_3.5x2.65mm

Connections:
5V_LED: C56.1, C58.1, C61.1, C63.1, C65.1, C67.1, C69.1, C70.1, C72.1, LED_ENC3.4, LED_ENC5.4, LED_ENC7.4, LED_ENC9.4, LED_ENC10.4, LED_ENC12.4, LED_ENC14.4, LED_ENC16.4, LED_STATUS.4, TP6.1
+3V3: C34.1, C36.1, F2.1, R2.1, R4.1, R6.1, R8.1, R9.1, R10.1, R14.1, R16.1, R18.1, R21.1, R23.1, R25.1, R27.1, R29.1, R30.1, R32.1, R34.1, R36.1, R38.1, R41.1, R43.1, R45.1, R47.1, R81.1, R83.1, R85.1, R87.1, R110.1, SW1.1, U1.9, U3.9, U3.16, U5.5
COL1: D19.1, D31.1, D37.1, D40.1, R81.2
COL2: D8.1, D17.1, D35.1
COL3: D15.1, R83.2
COL4: D1.1, D11.1, D22.1, D26.1
COL5: D6.1, D33.1, R85.2
COL6: D3.1, D13.1, D24.1, D28.1
COL7: D20.1, D39.1, D42.1, R87.2
ENC1_A: R49.2, U1.21
ENC1_B: C2.1, R50.2, U1.1
ENC1_B_RAW: R2.2, R50.1
ENC2_B: C4.1, R52.2, U1.2
ENC2_B_RAW: R4.2, R52.1
ENC2_SW: R34.2, U3.22
ENC3_A: C5.1, U1.23
ENC3_B: C6.1, R54.2, U1.3
ENC3_B_RAW: R6.2, R54.1
ENC4_B: R56.2, U1.4
ENC4_B_RAW: R8.2, R56.1
ENC4_SW: R36.2, U3.24
ENC5_B: C10.1, R58.2, U1.5
ENC5_B_RAW: R10.2, R58.1
ENC6_B: C12.1, U1.6
ENC6_SW: R38.2, U3.26
ENC7_A: R61.2, U1.27
ENC7_B: C14.1, U1.7
ENC8_A: R63.2, U1.28
ENC8_B: C16.1, U1.8
ENC9_A_RAW: ENC9.A, R65.1
ENC9_B_RAW: ENC9.B, R18.2
ENC9_SW: ENC9.S1, R41.2, U3.1
ENC10_A_RAW: ENC10.A, R67.1
ENC10_SW: ENC10.S1, U3.2
ENC11_A: C21.1, R69.2
ENC11_A_RAW: ENC11.A, R21.2, R69.1
ENC11_B_RAW: ENC11.B, R70.1
ENC11_SW: ENC11.S1, R43.2, U3.3
ENC12_A_RAW: ENC12.A, R23.2
ENC12_B_RAW: ENC12.B, R72.1
ENC12_SW: ENC12.S1, U3.4
ENC13_A_RAW: ENC13.A, R25.2
ENC13_B_RAW: ENC13.B, R74.1
ENC13_SW: ENC13.S1, R45.2, U3.5
ENC14_A_RAW: ENC14.A, R27.2
ENC14_B_RAW: ENC14.B, R76.1
ENC14_SW: ENC14.S1, U3.6
ENC15_A_RAW: ENC15.A, R29.2
ENC15_B: C30.1, R78.2
ENC15_B_RAW: ENC15.B, R30.2, R78.1
ENC15_SW: ENC15.S1, R47.2, U3.7
ENC16_B_RAW: ENC16.B, R32.2
ENC16_SW: ENC16.S1, U3.8
FADER2: C54.1, R105.2
FADER2_RAW: F2.2, R105.1
GATE_IN_BUF: R114.1, U5.4
GATE_IN_RAW: C51.1, R103.2, U5.2
GND: C2.2, C4.2, C5.2, C6.2, C10.2, C12.2, C14.2, C16.2, C18.2, C21.2, C23.2, C25.2, C27.2, C29.2, C30.2, C32.2, C34.2, C36.2, C38.2, C72.2, C80.2, C82.2, ENC9.C, ENC9.S2, ENC10.C, ENC10.S2, ENC11.C, ENC11.S2, ENC12.C, ENC12.S2, ENC13.C, ENC13.S2, ENC14.C, ENC14.S2, ENC15.C, ENC15.S2, ENC16.C, ENC16.S2, R112.1, R120.2, U1.10, U1.15, U1.16, U1.17, U3.10, U3.15, U3.17, U5.3, U8.2, U8.3
GNDA: C42.2, C44.2, C46.2, C48.2, C51.2, C54.2, D45.2, D47.2, D49.2, D50.2, D52.2, F2.3, J06.S, J07.S, J08.S, J09.S, J10.S, R112.2, TP8.1
INT: U1.20, U3.20
K_L11_N: D11.2, KEY_R01.2
K_L13_N: D13.2, KEY_R04.2
K_L15_N: D15.2, KEY_R08.2
K_L17_N: D17.2, KEY_R13.2
K_L19_N: D19.2, KEY_R16.2
K_L20_N: D20.2, KEY_R19.2
K_R12_N: D33.2, KEY_R03.2
K_R14_N: D35.2, KEY_R07.2
K_R16_N: D37.2, KEY_R10.2
K_R18_N: D39.2, KEY_R15.2
K_R19_N: D40.2, KEY_R17.2
K_R21_N: D42.2, KEY_R20.2
LED_CH9: LED_ENC9.1, LED_ENC10.3
LED_CH16: LED_ENC16.1, LED_STATUS.3
LED_RET: C56.2, C58.2, C61.2, C63.2, C65.2, C67.2, C69.2, C70.2, LED_ENC3.2, LED_ENC5.2, LED_ENC7.2, LED_ENC9.2, LED_ENC10.2, LED_ENC12.2, LED_ENC14.2, LED_ENC16.2, LED_STATUS.2
MCP_RST: U1.18, U3.18
MIC_DATA: R124.1, TP38.1
MIC_DATA_M: R124.2, U8.6
MIC_VDD: C82.1, FB1.2, U8.5
MIC_VDD_SW: C80.1, FB1.1, R120.1, SW1.2
MIC_WS_M: R122.2, U8.1
ROW2: KEY_R06.1, KEY_R11.1, KEY_R19.1
ROW3: KEY_R01.1, KEY_R02.1, KEY_R04.1, KEY_R08.1, KEY_R13.1, KEY_R16.1, KEY_R21.1
ROW5: KEY_R07.1, KEY_R10.1, KEY_R18.1
ROW6: KEY_R03.1, KEY_R05.1, KEY_R09.1, KEY_R12.1, KEY_R17.1, KEY_R20.1
SCL: TP2.1, U1.12, U3.12
SDA: R110.2, U1.13, U3.13
TIP_CVIN1: C46.1, R98.1
TIP_CVIN2: D49.1, J06.T
TIP_CVIN3: C48.1, D50.1, J07.T
TIP_CVIN4: J08.T, R101.1
TIP_CVOUT1: C42.1, R94.2
TIP_CVOUT3: C44.1, R96.2
TIP_GATE_IN: J10.T, R103.1
TIP_GATE_OUT: D52.1, J09.T

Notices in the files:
hardware/core2/CORE-2.kicad_sch:
Bukifon open hardware - CERN-OHL-S-2.0
